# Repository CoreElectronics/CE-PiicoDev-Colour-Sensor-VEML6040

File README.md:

# PiicoDev® Colour Sensor VEML6040

This is the repo for the Core Electronics [PiicoDev Colour Sensor VEML6040](https://core-electronics.com.au/catalog/product/view/sku/CE07823).

Use the PiicoDev® Colour Sensor to measure the RGBW components of light, or even extract the colour of an object so you can compare apples with oranges. Onboard is a high accuracy colour sensor - the VEML6040 boasts 16-bit precision for each channel (R, G, B, W). By using PiicoDev adapters and cables, you can connect to this sensor without soldering - or use the standard breakout header if you prefer breadboard prototyping. Whichever you prefer, the PiicoDev guides will get you measuring colour in no time!

### Features

Small size, high accuracy
Onboard High-CRI LED for measuring reflected light
Great guides to get you started
PiicoDev connector, compatible with Qwiic and STEMMA QT (3.3V only)
2.54mm breakout for breadboarding/prototyping
Manufactured and supported in Australia by Core Electronics

### Getting Started Guides

- For [Micro:bit](https://core-electronics.com.au/tutorials/micro-bit/piicodev-colour-sensor-veml6040-micro-bit-guide.html)
- For [Raspberry Pi Pico](https://core-electronics.com.au/tutorials/raspberry-pi-pico/piicodev-colour-sensor-veml6040-raspberry-pi-pico-guide.html)
- For [Raspberry Pi](https://core-electronics.com.au/tutorials/raspberry-pi/piicodev-colour-sensor-veml6040-raspberry-pi-guide.html)

### Technical Specifications

- Address: 0x10,
- 16-bit precision per channel
- Dimensions: 25.4x25.4mm
- Mounting Holes: 2x M2.5
- Disable LED by pulling LED Pin to Ground.

# License
This project is open source - please review the LICENSE.md file for further licensing information.

If you have any technical questions, or concerns about licensing, please contact technical support on the [Core Electronics forums](https://forum.core-electronics.com.au/).

*\"PiicoDev\" and the PiicoDev logo are trademarks of Core Electronics Pty Ltd.*

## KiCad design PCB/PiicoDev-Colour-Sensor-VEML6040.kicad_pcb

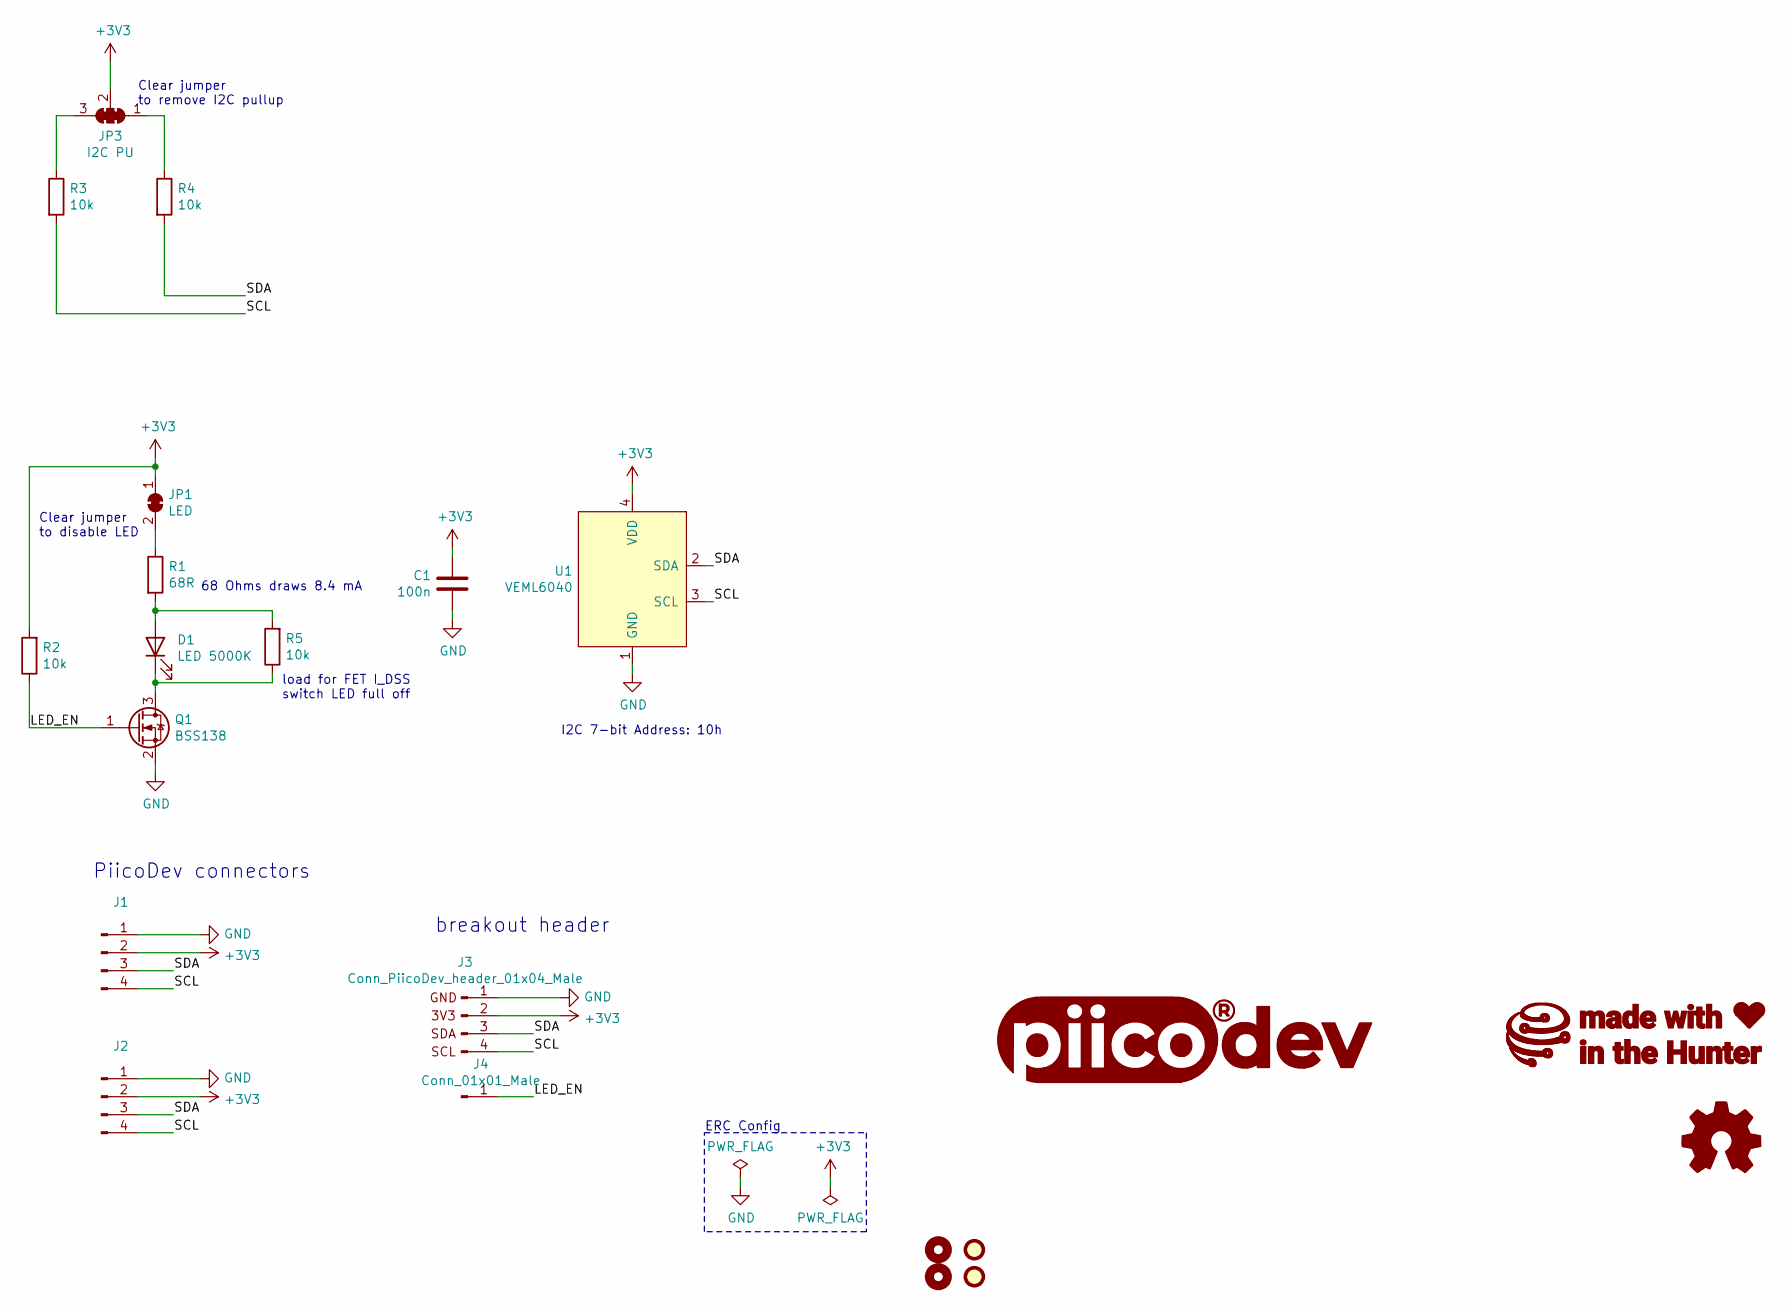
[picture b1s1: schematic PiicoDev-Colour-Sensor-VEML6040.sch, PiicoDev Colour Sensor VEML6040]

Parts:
C1: 100n; C_0402_1005Metric
D1: LED 5000K; LED_1208_3020Metric_Heatsink
FID1, FID2: Fiducial; Fiducial_1mm_Mask2mm
G1: LOGO_CoreElectronics_no-text; CoreElectronics_logo_5mm
G2: LOGO_piico; piicodev_logo_14.2x3.4mm
G3: LOGO_made-with-love; piicodev_logo_14.2x3.4mm
H1, H4: MountingHole; MountingHole_2.7mm_M2.5_PadClearance_1.2
J1, J2: JST_SH_SM04B-SRSS-TB_1x04-1MP_P1.00mm_Horizontal
J3: Conn_PiicoDev_header_01x04_Male; PiicoDev_header_4pin
J4: Conn_01x01_Male; PiicoDev_header_1pin_LED
JP1: LED; SolderJumper-2_P1.3mm_Bridged_RoundedPad1.0x1.5mm
JP3: I2C PU; SolderJumper-3_P1.3mm_Closed_RoundedPad1.0x1.5mm_NumberLabe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
LOGO1: Logo_Open_Hardware_Small; oshw
Q1: BSS138; SOT-23
R1: 68R; R_0402_1005Metric
R2, R3, R4, R5: 10k; R_0402_1005Metric
U1: VEML6040; VISHAY_VEML6040_2X1.25X1

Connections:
+3V3: C1.2, J1.2, J2.2, J3.2, JP1.1 (A), JP3.2 (C), R2.2, U1.4 (VDD)
/LED_EN: J4.1, Q1.1 (G), R2.1
/SCL: J1.4, J2.4, J3.4, R3.2, U1.3 (SCL)
/SDA: J1.3, J2.3, J3.3, R4.2, U1.2 (SDA)
GND: C1.1, J1.1, J2.1, J3.1, Q1.2 (S), U1.1 (GND)
unnamed: D1.1 (K), Q1.3 (D), R5.1
unnamed: D1.2 (A), R1.2, R5.2
unnamed: JP1.2 (B), R1.1
unnamed: JP3.1 (A), R4.1
unnamed: JP3.3 (B), R3.1

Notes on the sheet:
Clear jumper to remove I2C pullup
PiicoDev connectors
breakout header
I2C 7-bit Address: 10h
ERC Config
Clear jumper to disable LED
68 Ohms draws 8.4 mA
load for FET I_DSS switch LED full off

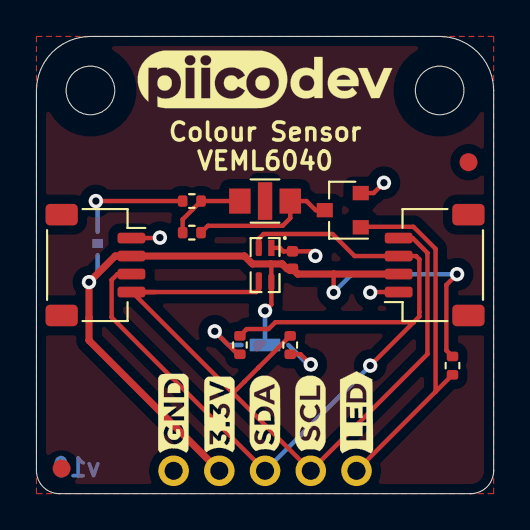
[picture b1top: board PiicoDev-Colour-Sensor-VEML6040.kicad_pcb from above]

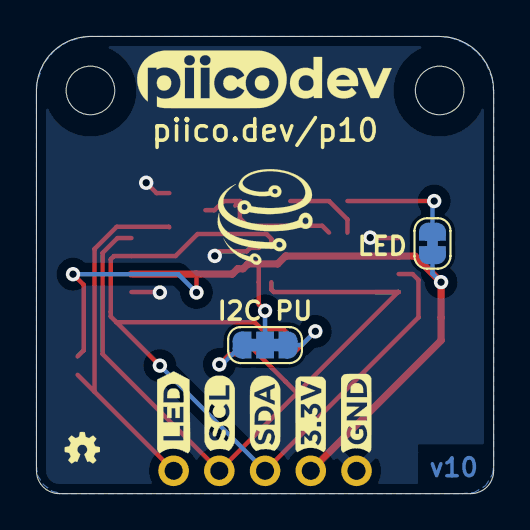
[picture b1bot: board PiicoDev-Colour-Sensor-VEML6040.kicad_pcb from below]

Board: 2 copper layers, 25.4 x 25.4 mm, 23 parts (7 on the bottom side), 10 nets.

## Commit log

2021-05-10 Replace power LED with illumination LED
2021-05-11 Update version number
2021-05-11 Tweak layout
2021-06-15 Add LED current note
2021-08-24 Add LED bypass resistor
2021-08-24 Change date
2021-11-04 Make LED_1208_3020 SMT instead of through-hole
2021-12-05 correct schematic pdf
2022-01-11 Change 4k7 resistors to 10k
2022-03-21 Update schematic-piicodev-colour-sensor-veml6040-v10.pdf
    update resistor values 4k7 to 10k

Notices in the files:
PCB/PiicoDev-Colour-Sensor-VEML6040.kicad_pcb:
License: CCASAv4.0 http://creativecommons.org/licenses/by-sa/4.0
